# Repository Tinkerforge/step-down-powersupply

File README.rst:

Step-Down Power Supply
======================

This repository contains the hardware design files for the Step-Down
Power Supply.

Repository Content
------------------

hardware/:
 * Contains kicad project files and additionally schematics as pdf

Hardware
--------

The hardware is designed with the open source EDA Suite KiCad
(http://www.kicad.org). Before you are able to open the files,
you have to install the Tinkerforge kicad-libraries
(https://github.com/Tinkerforge/kicad-libraries). You can either clone
them directly in hardware/ or clone them in a separate folder and
symlink them into hardware/
(ln -s kicad_path/kicad-libraries project_path/hardware). After that you
can open the .pro file in hardware/ with kicad and from there view and
modify the schematics and the PCB layout.

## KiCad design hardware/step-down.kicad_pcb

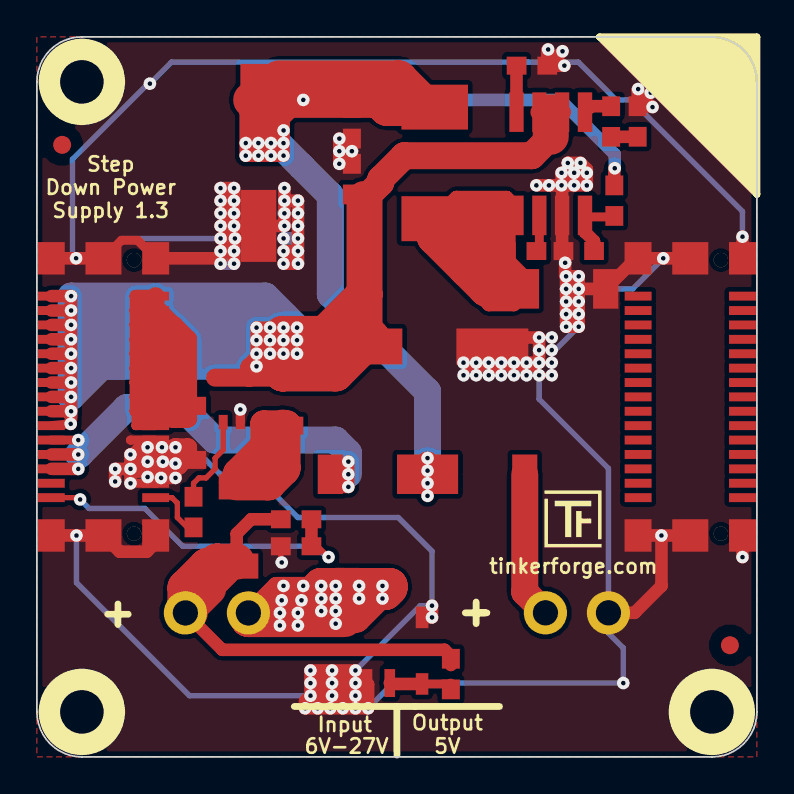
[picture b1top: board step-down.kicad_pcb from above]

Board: 2 copper layers, 40.0 x 40.0 mm, 38 parts (0 on the bottom side), 19 nets.

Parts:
C1: 220µF/35V; ELKO_83
C2, C5, C6: 100nF; C0603E
C3: 1µF/10V; C0603E
C4: 1nF; C0603E
C7: 470µF/16V; ELKO_83
D1: Z12V; SOD-123
D2, D3, D4, D5: PMEG4050BEP; SOD-128
FB1: FB; R1206
Fiducial_Mark: VAL**; Fiducial_Mark
Fiducial_Mark#2: VAL**; Fiducial_Mark
J1, J2: STACK-UP-HIGH; BTB08-ACS-TOP
L1: 10µH; SRP7030
P1: Black; OQ_2P
P2: Green; OQ_2P
Q1: FDS8449; SOIC-8-MOSFET
R1: 100k; R0603E
R2, R5: 10k; R0603E
R3: 1k; R0603E
R4: 0.01; R1206
R6, R8: 10k; C0603E
R7: 57.6k; C0603E
Ref**: Val**
U1: ZXCT1086; SOT23-5
U2: AOZ1212; SO-8
U3, U4, U5, U6: DRILL; DRILL_NP
VAL: WEEE_7mm
VAL#2: CE_5mm

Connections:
+5V: D4.2, J2.22, J2.24, J2.26
AGND: FB1.2, J2.1, J2.3, J2.5, J2.7, J2.9, J2.11, J2.13, J2.15, J2.17, J2.19
CURRENT: J2.29, R5.2
GND: C1.2, C2.2, C3.2, C4.2, C6.2, C7.2, D1.1, D3.1, FB1.1, J1.EP, J2.21, J2.23, J2.25, J2.27, J2.EP, P2.2, Q1.S, R3.2, R8.2, U1.2, U2.3
unnamed: C3.1, U2.8
unnamed: C4.1, R6.1
unnamed: C5.1, D3.2, L1.1, U2.1
unnamed: C5.2, U2.2
unnamed: C6.1, C7.1, D4.1, D5.1, L1.2, R7.1
unnamed: D1.2, Q1.G, R1.2
unnamed: D2.1, P1.1, R1.1, R2.1
unnamed: D2.2, R4.2, U1.3
unnamed: D5.2, P2.1
unnamed: P1.2, Q1.D
unnamed: R5.1, U1.1
unnamed: R6.2, U2.5
unnamed: R7.2, R8.1, U2.4
VOLTAGE: J2.30, R2.2, R3.1
VPP: C1.1, C2.1, J2.2, J2.4, J2.6, J2.8, J2.10, J2.12, J2.14, J2.16, J2.18, J2.20, R4.1, U1.4, U1.5, U2.6, U2.7

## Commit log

2011-08-26 add repository description
2013-12-02 add hardware files of version 1.2
2013-12-02 schematic in color fix input voltage hint
2015-05-07 start new prototype of step down power supply with filtered inputs, fuse and diode protected output
2015-05-07 change 0402 footprints to 0603
2015-05-18 updated version of new prototype, change current sensor, add filtering, not finished
2015-05-19 next routing test, vpp seems to be not routable
2015-05-19 routing finished
2016-12-28 change version 1.3, remove filters
2016-12-28 again drc check executed, project settings changed
2017-01-12 update pcb
2017-05-22 change components to new standard components, oder version
2017-06-02 Add 3d information (tbc)
2017-06-09 fix fab text positions
2017-06-09 Add missing 3d information
2017-06-09 Add 3d model (*.step and *.FCStd)
2017-06-16 Fix MOSFET_N to MOSFET_N_CH
2017-06-16 Add 3d information to components (tbc)
2017-06-23 Rename *.FCStd file
2017-08-03 add new version of step down power supply
2020-12-21 fix 3d modell
2021-10-25 Update KiCad link
    https://www.kicad.org/blog/2021/10/Avoid-links-to-former-kicad-domain/

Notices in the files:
hardware/step-down.kicad_pcb:
Licensed under CERN OHL v.1.1
Copyright (©) 2011, B.Nordmeyer
Copyright Tinkerforge GmbH 2012.
This documentation describes Open Hardware and is licensed under the
CERN OHL v. 1.1.
